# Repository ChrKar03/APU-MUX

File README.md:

# APU-MUX: Multiplexer System for UAV Autopilots

This repository contains the research, source code, and validation steps for a UAV Autopilot Multiplexer System. The project aims to create a redundancy mechanism that switches control between two Autopilot Units (APU) to a single set of actuators, enhancing the safety of Unmanned Aerial Vehicles (UAVs).

## 📖 Project Overview

The core function of this system is to act as a "coordinator" between two redundant autopilots. It operates with zero intelligence regarding flight dynamics, focusing solely on signal integrity and switching reliability.

Key Responsibilities:

    Sample Input: Capture PWM signals from APU #1 and APU #2.

    Reproduce Output: Generate a PWM signal for the actuators based on the selected input.

    Switching Logic: Select which APU controls the drone via a switching mechanism (GPIO trigger).

## 🛠 Hardware Architecture

The research was conducted in two phases using STMicroelectronics development boards.
### Phase 1: STM32G4 (Nucleo-G474RE)

Used for initial exploration of PWM input sampling and High-Resolution Timer (HRTIM) output.

    Input: 8 Timers (HTIMs) used in PWM Input mode to capture Period and Duty Cycle.

    Output: 4 High-Resolution Timers (HRTIMs).

    Limitation: The HRTIM hardware on the G4 requires a minimum system clock of 100MHz. This results in a minimum output PWM frequency of ~1526Hz, which is incompatible with standard 50Hz ESCs/Servos.

### Phase 2: STM32H7 (Dual Core M7 + M4)

The final implementation utilizes the STM32H755ZI (Nucleo-144) to overcome frequency limitations and introduce redundancy logic.

    M4 Core: Dedicated to "hard real-time" tasks: PWM sampling and forwarding.

    M7 Core: Handles "intelligent" tasks and serial communication.

    Clock Configuration: System clock set to 80MHz with timer clocks at 2.5MHz to support standard 50Hz PWM output.

## 💻 Software Implementation Strategy

This repository includes code for three distinct implementation approaches:
1. NVIC (Interrupt-Based)

    Mechanism: Uses global interrupts on input timers to capture PWM data.

    Pros: Simple implementation using HAL libraries.

    Cons: High CPU overhead. Performance degrades at high frequencies due to interrupt overload.

2. DMA (Direct Memory Access)

    Mechanism: Offloads CPU by transferring captured data directly from Input Timer registers to Output Timer registers.

    Memory Mapping: Exploits the memory layout of the STM32 peripherals. Since G4 registers have different bit-widths (16-bit reads vs 32-bit writes), the DMA handles the transfer to achieve autonomous updates.

    Performance: Works perfectly up to 30KHz input frequency with minimal CPU intervention.

3. Dual-Core Setup (STM32H7)

    Architecture:

        Shared Memory: Used to pass data between the M7 and M4 cores.

        Synchronization: Hardware Semaphores (HSEM) synchronize boot sequences and resource access.

## 🧪 Verification: Hardware-in-the-Loop (HITL)

To verify the hardware without risking a physical drone, a HITL environment was created using ArduPilot SITL and Gazebo.

Data Flow:

    Gazebo: Simulates physics and sends sensor data to SITL.

    ArduPilot SITL: Calculates motor outputs and sends them via UDP.

    stm32bridge.py: A Python script that acts as a bridge. It converts UDP packets to Serial data.

    STM32H7: Receives Serial data (M7), generates electrical PWM (M4), samples it back, and returns the read values to the script .

To run the verification experiment, refer to the scripts in the coordinator.py and stm32bridge.py files.
## 🔌 Pinout Configuration

### STM32G474RET

### STM32H755ZIT

Note: The system supports 8 inputs mapped to 4 high-resolution outputs.
## 📂 Repository Structure

    imgs/: Images used for this README.

    manuals/: pdf files for the STM32G4's and H7's documentation.

    src/: STM32CubeIDE projects of G4 and H7.

    scripts/: Contains the dma_script.py, nvic_script.py for the G4 and stm32bridge.py for testing H7 and HITL.

    board/: Contains a custom pcb implementation.

## ⚙️ Prerequisites

    IDE: STM32CubeIDE.

    Flash Tool: STM32CubeProgrammer.

    Simulation: ArduPilot SITL, Gazebo 8.10.

    Python Libraries: PyVISA, Serial libraries.

    ArduPilot: https://github.com/ArduPilot/ardupilot.git

    Gazebo 8.10: https://github.com/gazebosim 

    SITL_Gazebo plugin: https://github.com/ArduPilot/ardupilot_gazebo.git

## 📝 Credits

Author: Christos Karagiannis

Institution: University of Thessaly, Department of Electrical and Computer Engineering.

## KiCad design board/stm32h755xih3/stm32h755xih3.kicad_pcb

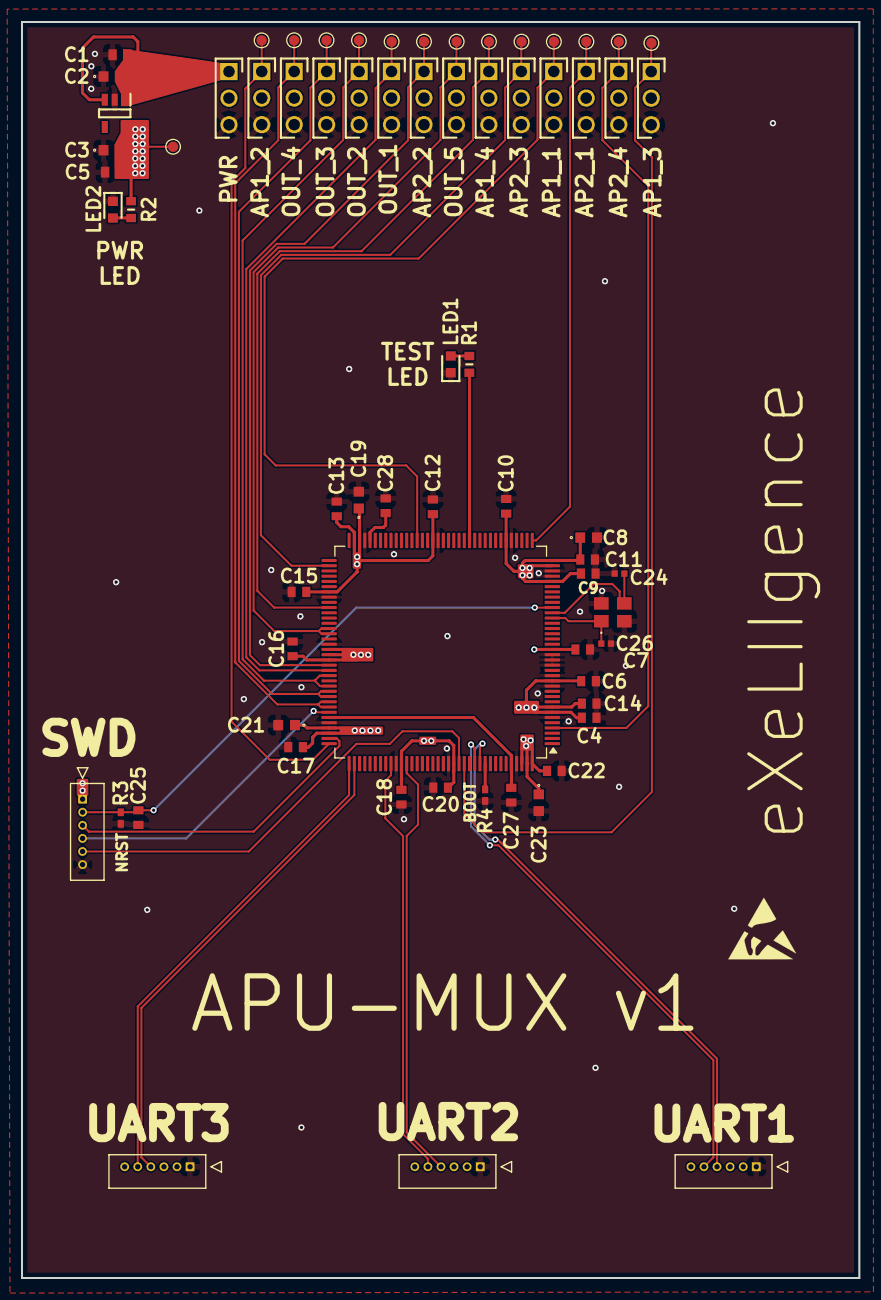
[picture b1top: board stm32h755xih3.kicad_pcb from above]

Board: 4 copper layers, 80.0 x 120.0 mm, 55 parts (0 on the bottom side), 34 nets.

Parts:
C1, C5: MLASG168BB5475KTNA01; CAPC1709X100N
C2, C3, C8, C19, C21, C23: C0603X105J4RACTU; C0603
C4, C6, C7, C9, C10, C11, C12, C13, C14, C15, C16, C17, C18, C20, C22, C25: CC0603JRX7R9BB104; CAPC1608X90N
C24, C26: GRM1555C1H8R0DA01D; CAPC1005X70N
C27, C28: 0603YC225MAT2A; CAPC1608X90N
IC1: AP2112K-3.3TRG1; SOT95P285X140-5N
J1, J2, J3, J5, J6, J7, J8, J10, J11, J12, J13, J15, J16, J17: HTSW-101-07-G-T; HDRV3W64P254_3X1_254X756X838P
J4, J9, J14, J18: 53047-0610; 530470610
LED1: LTST-C190KGKT; LEDC1608X80N
LED2: LTST-C190KRKT; LEDC1608X80N
R1, R2: RC0603FR-071KL; RESC1608X55N
R3, R4: RC0402FR-0710KL; RESC1005X40N
U1: STM32H755ZITx; LQFP-144_20x20mm_P0.5mm
Y1: 830059082; LFXTAL085880

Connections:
3V3: C3.2, C4.1, C5.1, C6.1, C7.1, C8.1, C9.1, C10.1, C11.1, C12.1, C13.1, C14.1, C15.1, C16.1, C17.1, C18.1, C19.1, C20.1, C21.1, C22.1, C23.1, IC1.5 (VOUT), J18.1, R2.1, U1.7 (VDD), U1.8 (VBAT), U1.13 (VDD), U1.19 (VDD), U1.32 (VDD), U1.35 (VREF+), U1.36 (VDDA), U1.42 (VDD), U1.56 (VDD), U1.70 (VDDLDO), U1.71 (VDD), U1.79 (VDD), U1.90 (VDD50_USB), U1.91 (VDD33_USB), U1.92 (VDD), U1.105 (VDDLDO), U1.106 (VDD), U1.119 (VDD), U1.129 (VDD), U1.142 (PDR_ON), U1.143 (VDDLDO), U1.144 (VDD)
AP1_1: J1.1, U1.59 (PE9)
AP1_2: J5.1, U1.108 (PA15)
AP1_3: J2.1, U1.131 (PB4)
AP1_4: J6.1, U1.82 (PD12)
AP2_1: J7.1, U1.37 (PA0)
AP2_2: J10.1, U1.93 (PC6)
AP2_3: J8.1, U1.74 (PB14)
AP2_4: J11.1, U1.4 (PE5)
BOOT: R4.1, U1.135 (BOOT0)
GND: C1.2, C2.1, C3.1, C4.2, C5.2, C6.2, C7.2, C8.2, C9.2, C10.2, C11.2, C12.2, C13.2, C14.2, C15.2, C16.2, C17.2, C18.2, C19.2, C20.2, C21.2, C22.2, C23.2, C24.2, C25.2, C26.1, C27.1, C28.1, IC1.2 (GND), J1.3, J2.3, J3.3, J4.1, J5.3, J6.3, J7.3, J8.3, J9.1, J10.3, J11.3, J12.3, J13.3, J14.1, J15.3, J16.3, J17.3, J18.6, LED1.1 (K), LED2.1 (K), R3.2, R4.2, U1.6 (VSS), U1.12 (VSS), U1.14 (VSSSMPS), U1.16 (VDDSMPS), U1.17 (VFBSMPS), U1.18 (VSS), U1.33 (VSS), U1.34 (VSSA), U1.41 (VSS), U1.55 (VSS), U1.69 (VSS), U1.80 (VSS), U1.89 (VSS), U1.104 (VSS), U1.118 (VSS), U1.128 (VSS), U1.141 (VSS), Y1.2 (GND_&_LID_1), Y1.4 (GND_&_LID_2)
NRESET: C25.1, J18.2, R3.1, U1.27 (NRST)
unnamed: C27.2, U1.103 (VCAP), U1.140 (VCAP)
unnamed: C28.2, U1.68 (VCAP)
unnamed: C1.1, C2.2, IC1.1 (VIN), IC1.3 (EN), J3.1
unnamed: LED1.2 (A), R1.2
unnamed: LED2.2 (A), R2.2
OSC1: C26.2, U1.25 (PH0), Y1.1 (CRYSTAL_1)
OSC2: C24.1, U1.26 (PH1), Y1.3 (CRYSTAL_2)
RXD1: J4.4, U1.134 (PB7)
RXD2: J9.4, U1.120 (PD6)
RXD3: J14.4, U1.110 (PC11)
STM32B1/2: J15.1, U1.95 (PC8), U1.97 (PA8)
STM32C1/2: J17.1, U1.98 (PA9), U1.99 (PA10)
STM32D1/2: J13.1, U1.100 (PA11), U1.101 (PA12)
STM32E1/2: J16.1, U1.86 (PG6), U1.87 (PG7)
STM32Α1/2: J12.1, U1.94 (PC7)
SWCLK: J18.3, U1.107 (PA14)
SWDIO: J18.4, U1.102 (PA13)
SWO: J18.5, U1.130 (PB3)
TESTLED: R1.1, U1.49 (PB0)
TXD1: J4.5, U1.133 (PB6)
TXD2: J9.5, U1.117 (PD5)
TXD3: J14.5, U1.109 (PC10)

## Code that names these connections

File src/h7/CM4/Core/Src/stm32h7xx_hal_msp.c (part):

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    __HAL_RCC_GPIOC_CLK_ENABLE();
    __HAL_RCC_GPIOA_CLK_ENABLE();
    /**HRTIM GPIO Configuration
    PG6     ------> HRTIM_CHE1
    PC7     ------> HRTIM_CHA2
    PA8     ------> HRTIM_CHB2
    PA9     ------> HRTIM_CHC1
    */
    GPIO_InitStruct.Pin = GPIO_PIN_6;
    GPIO_InitStruct.Mode = GPIO_MODE_AF_PP;
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
    __HAL_RCC_GPIOE_CLK_ENABLE();
    /**TIM1 GPIO Configuration
    PE9     ------> TIM1_CH1
    */
    GPIO_InitStruct.Pin = GPIO_PIN_9;
    GPIO_InitStruct.Mode = GPIO_MODE_AF_PP;
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
    __HAL_RCC_GPIOA_CLK_ENABLE();
    /**TIM2 GPIO Configuration
    PA15 (JTDI)     ------> TIM2_CH1
    */
    GPIO_InitStruct.Pin = GPIO_PIN_15;
    GPIO_InitStruct.Mode = GPIO_MODE_AF_PP;
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
    __HAL_RCC_GPIOB_CLK_ENABLE();
    /**TIM3 GPIO Configuration
    PB4 (NJTRST)     ------> TIM3_CH1
    */
    GPIO_InitStruct.Pin = GPIO_PIN_4;
    GPIO_InitStruct.Mode = GPIO_MODE_AF_PP;
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
    __HAL_RCC_GPIOD_CLK_ENABLE();
    /**TIM4 GPIO Configuration
    PD12     ------> TIM4_CH1
    */
    GPIO_InitStruct.Pin = GPIO_PIN_12;
    GPIO_InitStruct.Mode = GPIO_MODE_AF_PP;
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
    __HAL_RCC_GPIOA_CLK_ENABLE();
    /**TIM5 GPIO Configuration
    PA0     ------> TIM5_CH1
    */
    GPIO_InitStruct.Pin = GPIO_PIN_0;
    GPIO_InitStruct.Mode = GPIO_MODE_AF_PP;
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
    __HAL_RCC_GPIOC_CLK_ENABLE();
    /**TIM8 GPIO Configuration
    PC6     ------> TIM8_CH1
    */
    GPIO_InitStruct.Pin = GPIO_PIN_6;
    GPIO_InitStruct.Mode = GPIO_MODE_AF_PP;
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
    __HAL_RCC_GPIOB_CLK_ENABLE();
    /**TIM12 GPIO Configuration
    PB14     ------> TIM12_CH1
    */
    GPIO_InitStruct.Pin = GPIO_PIN_14;
    GPIO_InitStruct.Mode = GPIO_MODE_AF_PP;
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
    __HAL_RCC_GPIOE_CLK_ENABLE();
    /**TIM15 GPIO Configuration
    PE5     ------> TIM15_CH1
    */
    GPIO_InitStruct.Pin = GPIO_PIN_5;
    GPIO_InitStruct.Mode = GPIO_MODE_AF_PP;
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    __HAL_RCC_TIM1_CLK_DISABLE();

    /**TIM1 GPIO Configuration
    PE9     ------> TIM1_CH1
    */
    HAL_GPIO_DeInit(GPIOE, GPIO_PIN_9);

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    __HAL_RCC_TIM2_CLK_DISABLE();

    /**TIM2 GPIO Configuration
    PA15 (JTDI)     ------> TIM2_CH1
    */
    HAL_GPIO_DeInit(GPIOA, GPIO_PIN_15);

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    __HAL_RCC_TIM3_CLK_DISABLE();

    /**TIM3 GPIO Configuration
    PB4 (NJTRST)     ------> TIM3_CH1
    */
    HAL_GPIO_DeInit(GPIOB, GPIO_PIN_4);

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    __HAL_RCC_TIM4_CLK_DISABLE();

    /**TIM4 GPIO Configuration
    PD12     ------> TIM4_CH1
    */
    HAL_GPIO_DeInit(GPIOD, GPIO_PIN_12);

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    __HAL_RCC_TIM5_CLK_DISABLE();

    /**TIM5 GPIO Configuration
    PA0     ------> TIM5_CH1
    */
    HAL_GPIO_DeInit(GPIOA, GPIO_PIN_0);

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    __HAL_RCC_TIM8_CLK_DISABLE();

    /**TIM8 GPIO Configuration
    PC6     ------> TIM8_CH1
    */
    HAL_GPIO_DeInit(GPIOC, GPIO_PIN_6);

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    __HAL_RCC_TIM12_CLK_DISABLE();

    /**TIM12 GPIO Configuration
    PB14     ------> TIM12_CH1
    */
    HAL_GPIO_DeInit(GPIOB, GPIO_PIN_14);

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    __HAL_RCC_TIM15_CLK_DISABLE();

    /**TIM15 GPIO Configuration
    PE5     ------> TIM15_CH1
    */
    HAL_GPIO_DeInit(GPIOE, GPIO_PIN_5);

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
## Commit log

2026-02-13 updated image
2026-02-16 stm project implementations
2026-03-04 apu-mux v1
2026-03-04 Document custom PCB implementation in README
    Added section for custom PCB implementation.
2026-03-05 HITL for STM32H7
2026-03-05 added the kikad project for the pcb
2026-03-14 pcb updated
2026-03-14 pcb update
2026-03-14 f4,g4,h7 and scripts
2026-03-14 cleanup
2026-03-18 board updates
2026-03-18 board clearance
2026-03-20 board final???
2026-03-20 final??
2026-03-22 final?
2026-03-22 final???

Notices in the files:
src/h7/CM4/Core/Src/stm32h7xx_hal_msp.c:
Copyright (c) 2026 STMicroelectronics.
All rights reserved.
This software is licensed under terms that can be found in the LICENSE file
